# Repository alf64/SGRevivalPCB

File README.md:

# SGRevivalPCB
PCB for SGRevival

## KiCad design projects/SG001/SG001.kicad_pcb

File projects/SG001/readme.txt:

Grid used for most of the board elements: 5 mils.
Grid used for board edge cut: 0,1 mm.

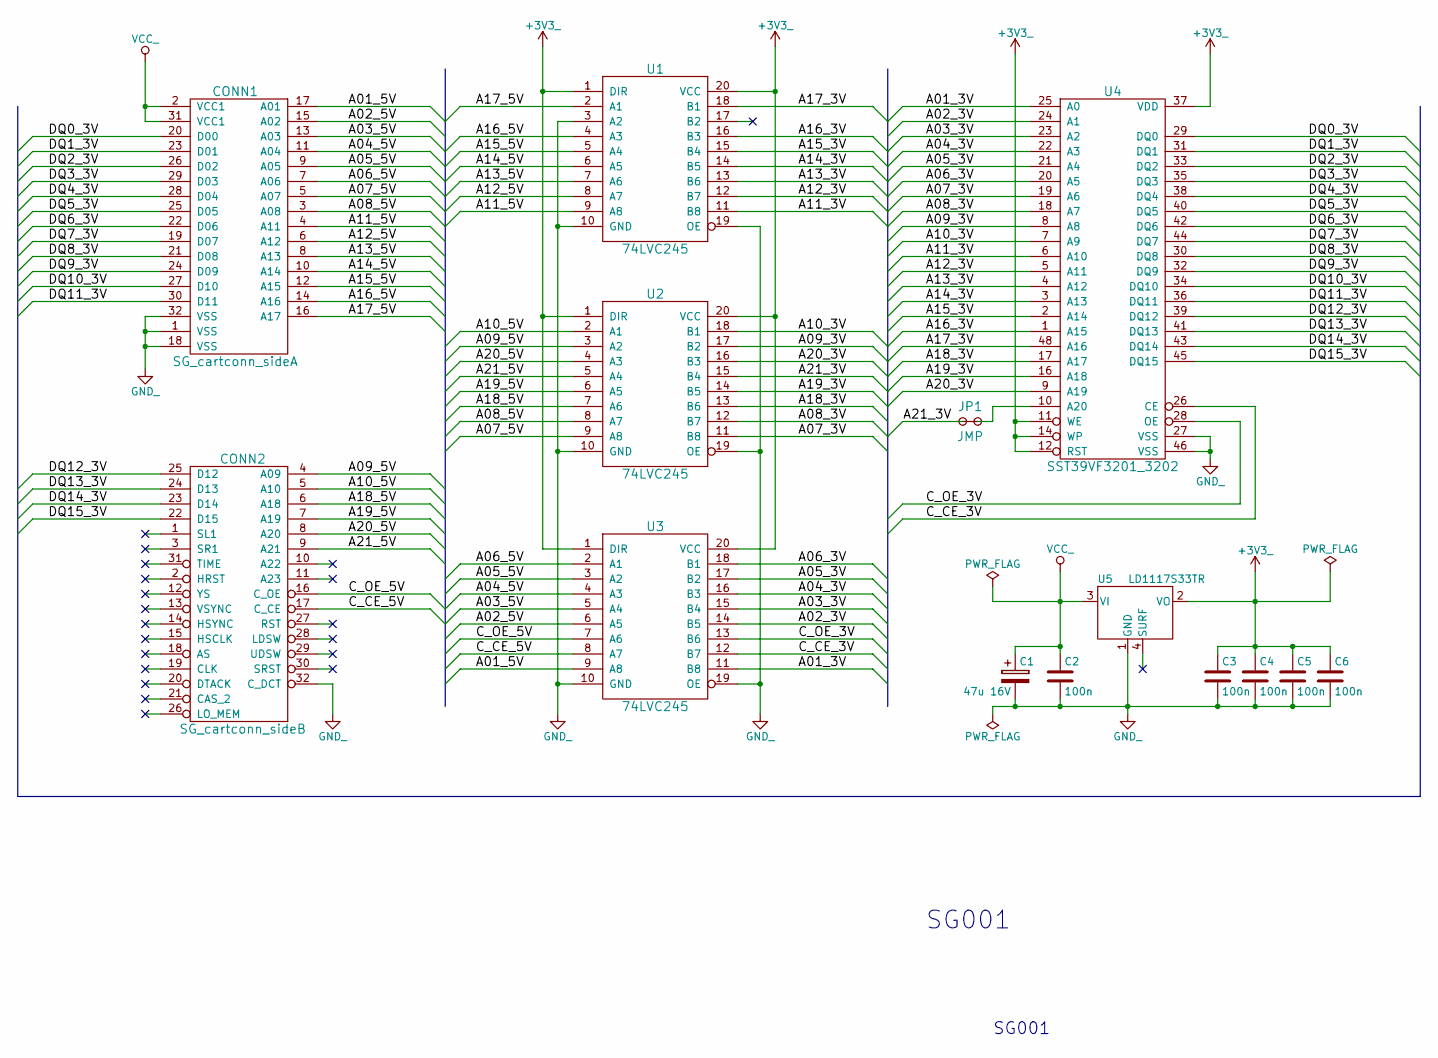
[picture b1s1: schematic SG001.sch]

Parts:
C1: 47u 16V; 2312
C2, C3, C4, C5, C6: 100n; 0805
CONN1: SG_cartconn_sideA; SG_cartconn
CONN2: SG_cartconn_sideB; SG_cartconn
JP1: JMP; JMP1_SMD
U1, U2, U3: 74LVC245; TSSOP20
U4: SST39VF3201_3202; TSOP48_SST
U5: LD1117S33TR; SOT223

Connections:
+3V3_: C3.1, C4.1, C5.1, C6.1, U1.1 (DIR), U1.20 (VCC), U2.1 (DIR), U2.20 (VCC), U3.1 (DIR), U3.20 (VCC), U4.11 (WE), U4.12 (RST), U4.14 (WP), U4.37 (VDD), U5.2 (VO)
/A01_3V: U3.11 (B8), U4.25 (A0)
/A01_5V: CONN1.17 (A01), U3.9 (A8)
/A02_3V: U3.14 (B5), U4.24 (A1)
/A02_5V: CONN1.15 (A02), U3.6 (A5)
/A03_3V: U3.15 (B4), U4.23 (A2)
/A03_5V: CONN1.13 (A03), U3.5 (A4)
/A04_3V: U3.16 (B3), U4.22 (A3)
/A04_5V: CONN1.11 (A04), U3.4 (A3)
/A05_3V: U3.17 (B2), U4.21 (A4)
/A05_5V: CONN1.9 (A05), U3.3 (A2)
/A06_3V: U3.18 (B1), U4.20 (A5)
/A06_5V: CONN1.7 (A06), U3.2 (A1)
/A07_3V: U2.11 (B8), U4.19 (A6)
/A07_5V: CONN1.5 (A07), U2.9 (A8)
/A08_3V: U2.12 (B7), U4.18 (A7)
/A08_5V: CONN1.3 (A08), U2.8 (A7)
/A09_3V: U2.17 (B2), U4.8 (A8)
/A09_5V: CONN2.4 (A09), U2.3 (A2)
/A10_3V: U2.18 (B1), U4.7 (A9)
/A10_5V: CONN2.5 (A10), U2.2 (A1)
/A11_3V: U1.11 (B8), U4.6 (A10)
/A11_5V: CONN1.4 (A11), U1.9 (A8)
/A12_3V: U1.12 (B7), U4.5 (A11)
/A12_5V: CONN1.6 (A12), U1.8 (A7)
/A13_3V: U1.13 (B6), U4.4 (A12)
/A13_5V: CONN1.8 (A13), U1.7 (A6)
/A14_3V: U1.14 (B5), U4.3 (A13)
/A14_5V: CONN1.10 (A14), U1.6 (A5)
/A15_3V: U1.15 (B4), U4.2 (A14)
/A15_5V: CONN1.12 (A15), U1.5 (A4)
/A16_3V: U1.16 (B3), U4.1 (A15)
/A16_5V: CONN1.14 (A16), U1.4 (A3)
/A17_3V: U1.18 (B1), U4.48 (A16)
/A17_5V: CONN1.16 (A17), U1.2 (A1)
/A18_3V: U2.13 (B6), U4.17 (A17)
/A18_5V: CONN2.6 (A18), U2.7 (A6)
/A19_3V: U2.14 (B5), U4.16 (A18)
/A19_5V: CONN2.7 (A19), U2.6 (A5)
/A20_3V: U2.16 (B3), U4.9 (A19)
/A20_5V: CONN2.8 (A20), U2.4 (A3)
/A21_3V: JP1.1 (A), U2.15 (B4)
/A21_5V: CONN2.9 (A21), U2.5 (A4)
/C_CE_3V: U3.12 (B7), U4.26 (CE)
/C_CE_5V: CONN2.17 (C_CE), U3.8 (A7)
/C_OE_3V: U3.13 (B6), U4.28 (OE)
/C_OE_5V: CONN2.16 (C_OE), U3.7 (A6)
/DQ0_3V: CONN1.20 (D00), U4.29 (DQ0)
/DQ1_3V: CONN1.23 (D01), U4.31 (DQ1)
/DQ2_3V: CONN1.26 (D02), U4.33 (DQ2)
/DQ3_3V: CONN1.29 (D03), U4.35 (DQ3)
/DQ4_3V: CONN1.28 (D04), U4.38 (DQ4)
/DQ5_3V: CONN1.25 (D05), U4.40 (DQ5)
/DQ6_3V: CONN1.22 (D06), U4.42 (DQ6)
/DQ7_3V: CONN1.19 (D07), U4.44 (DQ7)
/DQ8_3V: CONN1.21 (D08), U4.30 (DQ8)
/DQ9_3V: CONN1.24 (D09), U4.32 (DQ9)
/DQ10_3V: CONN1.27 (D10), U4.34 (DQ10)
/DQ11_3V: CONN1.30 (D11), U4.36 (DQ11)
/DQ12_3V: CONN2.25 (D12), U4.39 (DQ12)
/DQ13_3V: CONN2.24 (D13), U4.41 (DQ13)
/DQ14_3V: CONN2.23 (D14), U4.43 (DQ14)
/DQ15_3V: CONN2.22 (D15), U4.45 (DQ15)
GND_: C1.2, C2.2, C3.2, C4.2, C5.2, C6.2, CONN1.1 (VSS), CONN1.18 (VSS), CONN1.32 (VSS), CONN2.32 (C_DCT), U1.3 (A2), U1.10 (GND), U1.19 (OE), U2.10 (GND), U2.19 (OE), U3.10 (GND), U3.19 (OE), U4.27 (VSS), U4.46 (VSS), U5.1 (GND)
unnamed: JP1.2 (B), U4.10 (A20)
VCC_: C1.1, C2.1, CONN1.2 (VCC1), CONN1.31 (VCC1), U5.3 (VI)

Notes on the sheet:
SG001

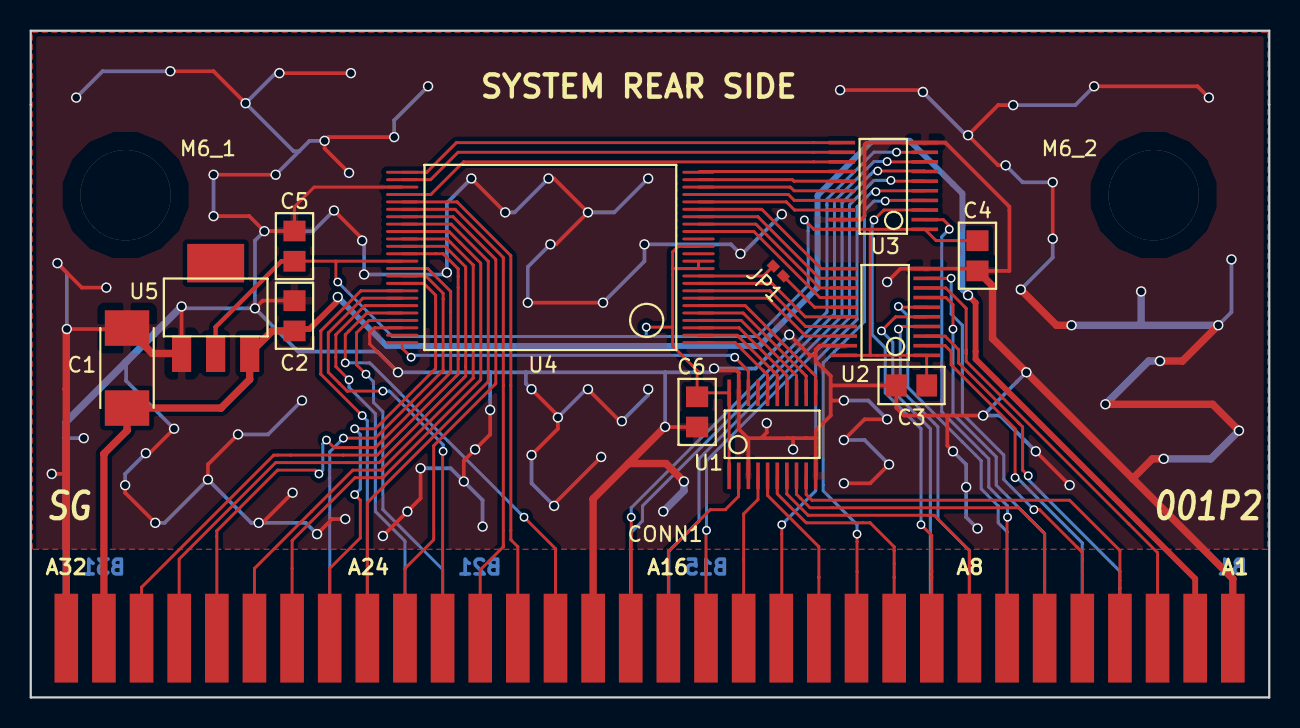
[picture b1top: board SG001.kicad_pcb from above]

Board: 2 copper layers, 83.6 x 45.0 mm, 16 parts (1 on the bottom side), 66 nets.

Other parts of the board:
M6_1, M6_2: HOLE_M6

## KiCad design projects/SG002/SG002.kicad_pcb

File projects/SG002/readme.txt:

Grid used for most of the board elements: 10 mils.
Grid used for board edge cut: 0,1 mm.

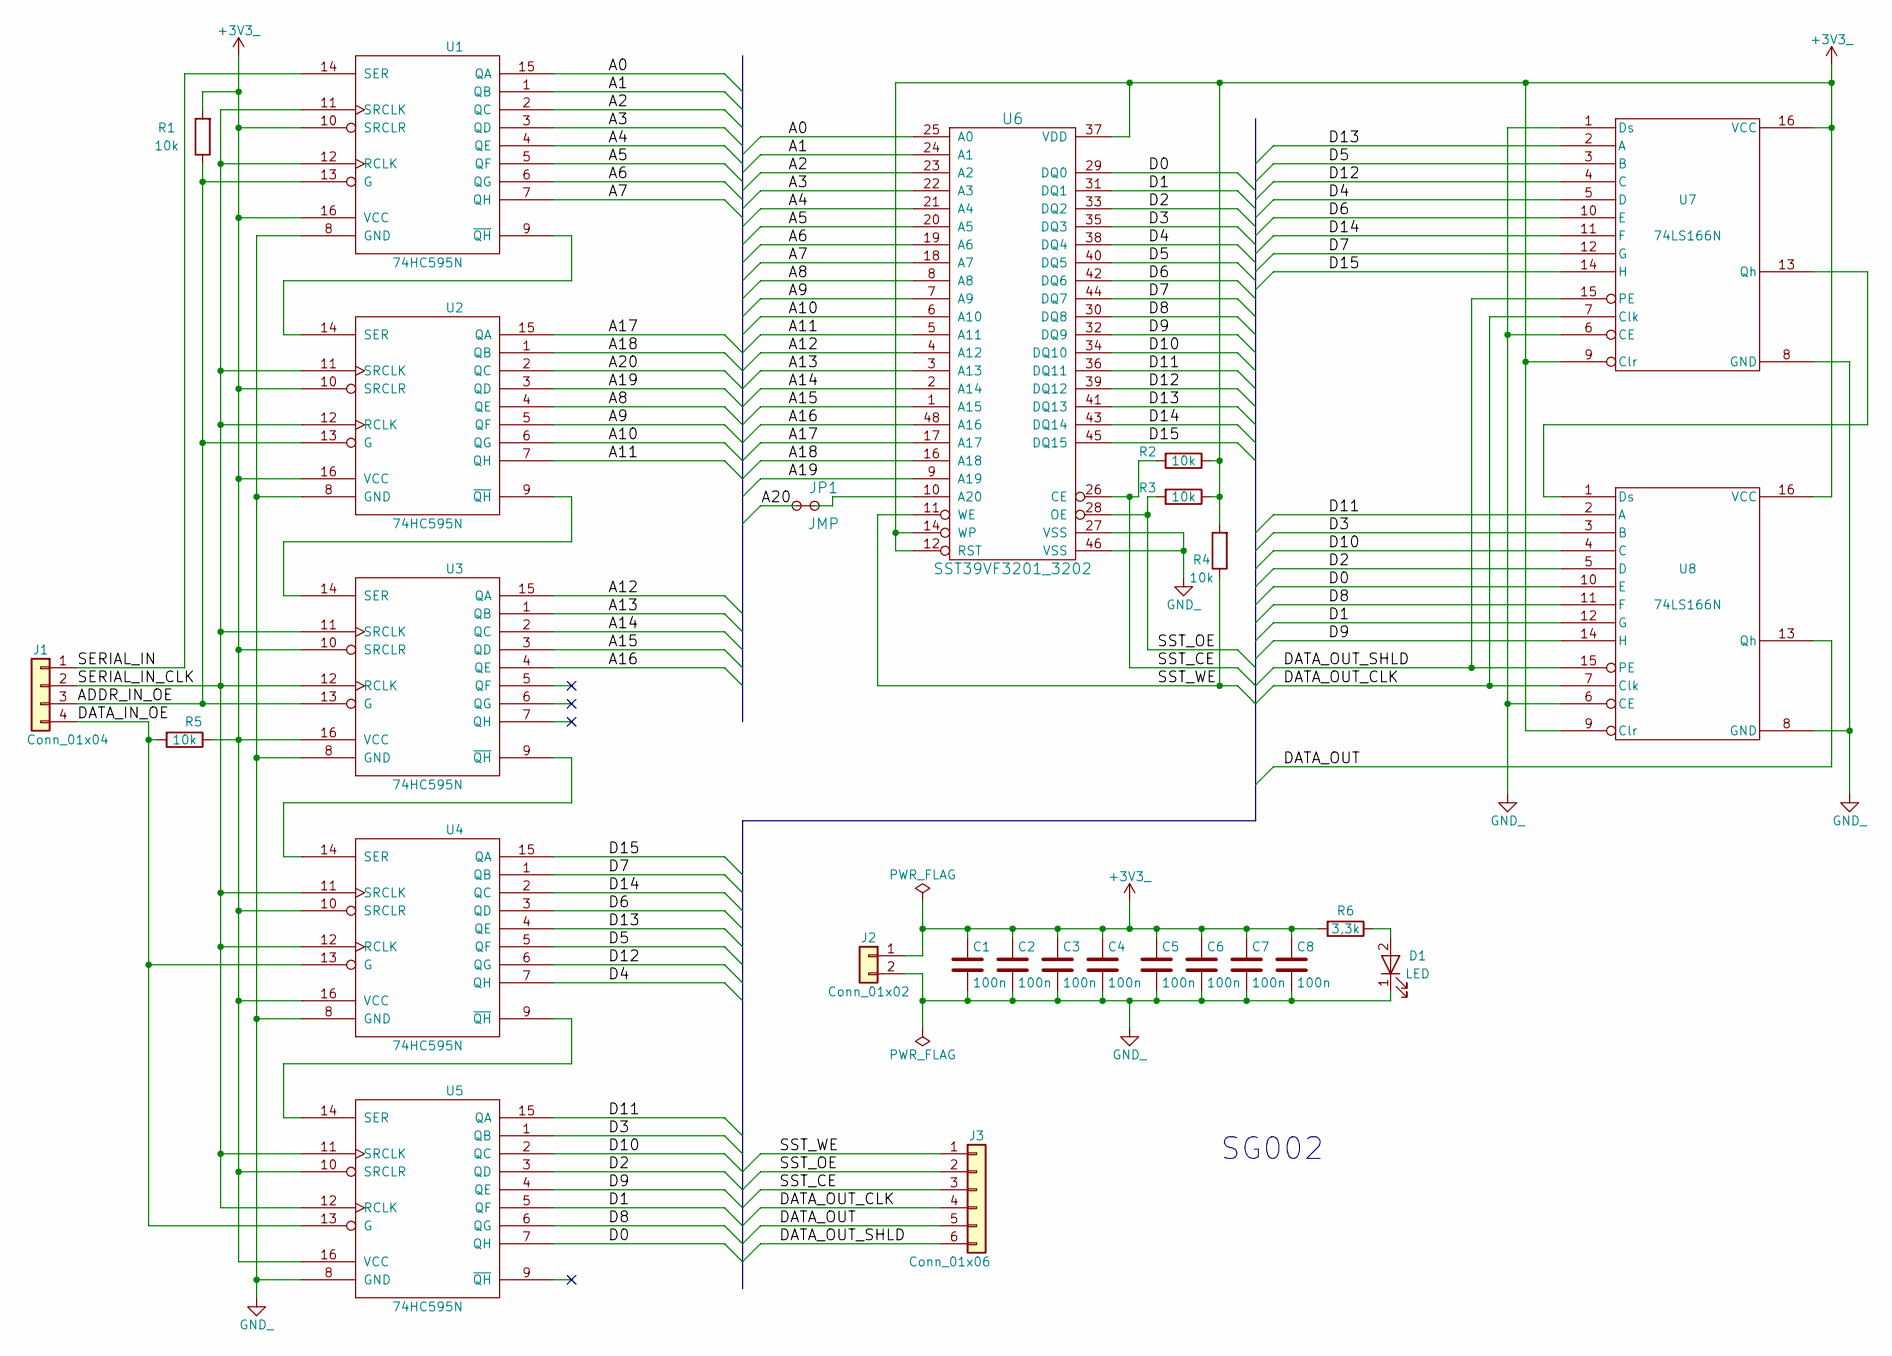
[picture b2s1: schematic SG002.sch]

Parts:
C1, C2, C3, C4, C5, C6, C7, C8: 100n; 0805
D1: LED; 0805
J1: Conn_01x04; PINHEAD1x4
J2: Conn_01x02; PINHEAD1x2
J3: Conn_01x06; PINHEAD1x6
JP1: JMP; PINHEAD1x2
R1, R2, R3, R4, R5: 10k; 0805
R6: 3,3k; 0805
U1, U2, U3, U4, U5: 74HC595N; SO16
U6: SST39VF3201_3202; DIP48
U7, U8: 74LS166N; SO16

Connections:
+3V3_: C1.1, C2.1, C3.1, C4.1, C5.1, C6.1, C7.1, C8.1, J2.1, R1.2, R2.1, R3.1, R4.2, R5.1, R6.2, U1.10 (SRCLR), U1.16 (VCC), U2.10 (SRCLR), U2.16 (VCC), U3.10 (SRCLR), U3.16 (VCC), U4.10 (SRCLR), U4.16 (VCC), U5.10 (SRCLR), U5.16 (VCC), U6.12 (RST), U6.14 (WP), U6.37 (VDD), U7.9 (Clr), U7.16 (VCC), U8.9 (Clr), U8.16 (VCC)
/A0: U1.15 (QA), U6.25 (A0)
/A1: U1.1 (QB), U6.24 (A1)
/A2: U1.2 (QC), U6.23 (A2)
/A3: U1.3 (QD), U6.22 (A3)
/A4: U1.4 (QE), U6.21 (A4)
/A5: U1.5 (QF), U6.20 (A5)
/A6: U1.6 (QG), U6.19 (A6)
/A7: U1.7 (QH), U6.18 (A7)
/A8: U2.4 (QE), U6.8 (A8)
/A9: U2.5 (QF), U6.7 (A9)
/A10: U2.6 (QG), U6.6 (A10)
/A11: U2.7 (QH), U6.5 (A11)
/A12: U3.15 (QA), U6.4 (A12)
/A13: U3.1 (QB), U6.3 (A13)
/A14: U3.2 (QC), U6.2 (A14)
/A15: U3.3 (QD), U6.1 (A15)
/A16: U3.4 (QE), U6.48 (A16)
/A17: U2.15 (QA), U6.17 (A17)
/A18: U2.1 (QB), U6.16 (A18)
/A19: U2.3 (QD), U6.9 (A19)
/A20: JP1.1 (A), U2.2 (QC)
/ADDR_IN_OE: J1.3, R1.1, U1.13 (G), U2.13 (G), U3.13 (G)
/D0: U5.7 (QH), U6.29 (DQ0), U8.10 (E)
/D1: U5.5 (QF), U6.31 (DQ1), U8.12 (G)
/D2: U5.3 (QD), U6.33 (DQ2), U8.5 (D)
/D3: U5.1 (QB), U6.35 (DQ3), U8.3 (B)
/D4: U4.7 (QH), U6.38 (DQ4), U7.5 (D)
/D5: U4.5 (QF), U6.40 (DQ5), U7.3 (B)
/D6: U4.3 (QD), U6.42 (DQ6), U7.10 (E)
/D7: U4.1 (QB), U6.44 (DQ7), U7.12 (G)
/D8: U5.6 (QG), U6.30 (DQ8), U8.11 (F)
/D9: U5.4 (QE), U6.32 (DQ9), U8.14 (H)
/D10: U5.2 (QC), U6.34 (DQ10), U8.4 (C)
/D11: U5.15 (QA), U6.36 (DQ11), U8.2 (A)
/D12: U4.6 (QG), U6.39 (DQ12), U7.4 (C)
/D13: U4.4 (QE), U6.41 (DQ13), U7.2 (A)
/D14: U4.2 (QC), U6.43 (DQ14), U7.11 (F)
/D15: U4.15 (QA), U6.45 (DQ15), U7.14 (H)
/DATA_IN_OE: J1.4, R5.2, U4.13 (G), U5.13 (G)
/DATA_OUT: J3.5, U8.13 (Qh)
/DATA_OUT_CLK: J3.4, U7.7 (Clk), U8.7 (Clk)
/DATA_OUT_SHLD: J3.6, U7.15 (PE), U8.15 (PE)
/SERIAL_IN: J1.1, U1.14 (SER)
/SERIAL_IN_CLK: J1.2, U1.11 (SRCLK), U1.12 (RCLK), U2.11 (SRCLK), U2.12 (RCLK), U3.11 (SRCLK), U3.12 (RCLK), U4.11 (SRCLK), U4.12 (RCLK), U5.11 (SRCLK), U5.12 (RCLK)
/SST_CE: J3.3, R2.2, U6.26 (CE)
/SST_OE: J3.2, R3.2, U6.28 (OE)
/SST_WE: J3.1, R4.1, U6.11 (WE)
GND_: C1.2, C2.2, C3.2, C4.2, C5.2, C6.2, C7.2, C8.2, D1.1 (K), J2.2, U1.8 (GND), U2.8 (GND), U3.8 (GND), U4.8 (GND), U5.8 (GND), U6.27 (VSS), U6.46 (VSS), U7.1 (Ds), U7.6 (CE), U7.8 (GND), U8.6 (CE), U8.8 (GND)
unnamed: D1.2 (A), R6.1
unnamed: JP1.2 (B), U6.10 (A20)
unnamed: U1.9 (~QH), U2.14 (SER)
unnamed: U2.9 (~QH), U3.14 (SER)
unnamed: U3.9 (~QH), U4.14 (SER)
unnamed: U4.9 (~QH), U5.14 (SER)
unnamed: U7.13 (Qh), U8.1 (Ds)

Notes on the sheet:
SG002

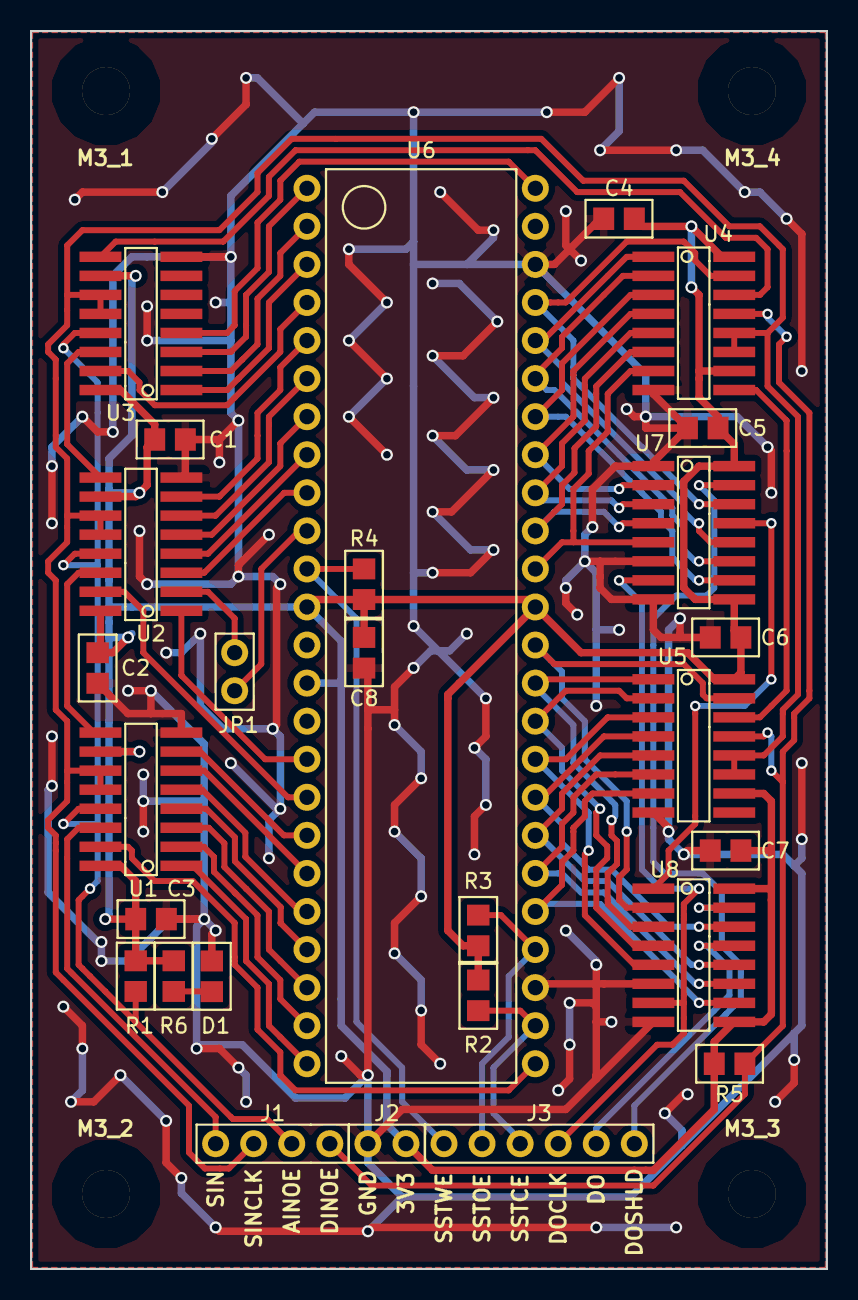
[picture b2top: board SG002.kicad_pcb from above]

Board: 2 copper layers, 53.1 x 82.6 mm, 31 parts (0 on the bottom side), 56 nets.

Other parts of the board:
M3_1, M3_2, M3_3, M3_4: MOUNTHOLE_M3

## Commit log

2021-05-12 Introduced SG001 and SG002.
2021-05-22 SG002 board initially completed.
2021-05-24 SG002 completed and gerbers released as SG002P1.
2021-06-28 SG001 initially completed.
2021-07-01 SG001 completed.
2021-07-02 SG001 fixes, gerbers generated and board released as SG001P1.
2021-07-02 SG001 40mm dimension increased to 45mm, because of manufacturer request (board needs to be at least 45mm wide for bevelling to be possible to apply) SG001 gerbers re-generated and board released as S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
